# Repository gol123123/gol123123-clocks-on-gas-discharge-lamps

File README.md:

# Clocks-on-gas-discharge-lamps
Мой первый проект с использованием микроконтроллера STM32 и газоразрядных ламп.
# Демонстрация

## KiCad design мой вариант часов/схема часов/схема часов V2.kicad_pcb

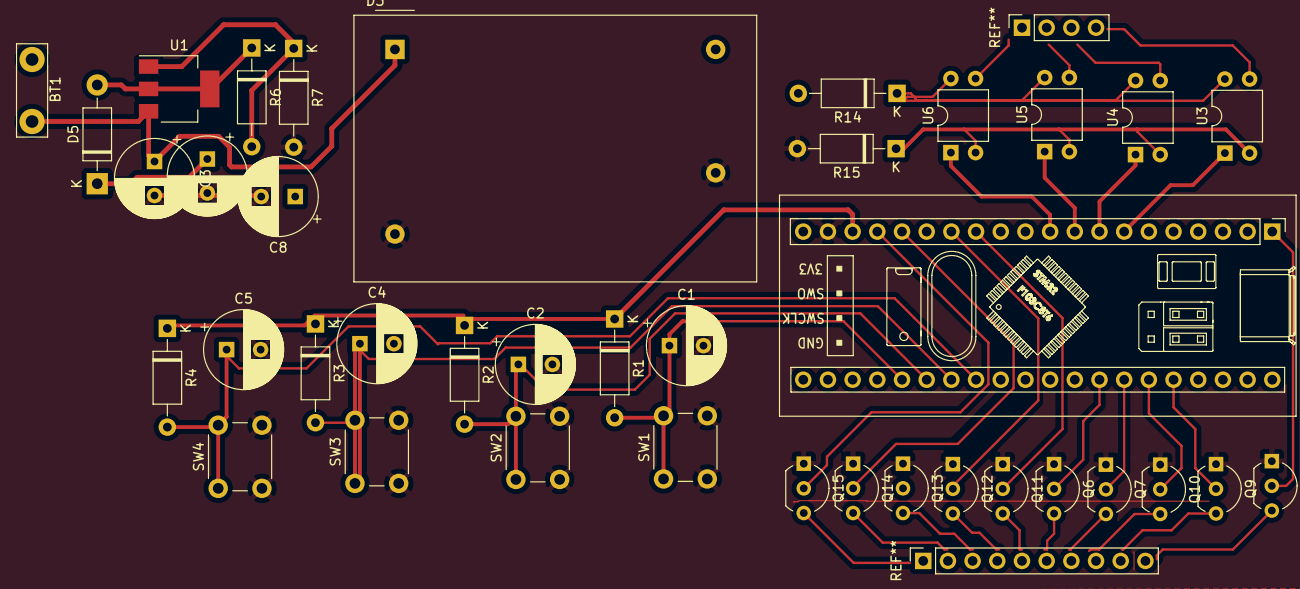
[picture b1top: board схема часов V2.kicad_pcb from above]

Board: 2 copper layers, 38 parts (0 on the bottom side), 26 nets.

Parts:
BT1: Battery_Cell; TestPoint_Bridge_Pitch6.35mm_Drill1.3mm
C1, C2, C4, C5, C8: 1u; CP_Radial_D8.0mm_P3.50mm
C3: 0.1u; CP_Radial_D8.0mm_P3.50mm
C7: 10u; CP_Radial_D8.0mm_P3.50mm
D3: dc-ac_180v; Converter_ACDC_TRACO_TMG-15_THT
D5: 1N4002; D_DO-41_SOD81_P10.16mm_Horizontal
Q6, Q7, Q8, Q9, Q10, Q11, Q12, Q13, Q14, Q15: MPSA42; TO-92_Inline_Wide
R1, R2, R3, R4: 1k; D_A-405_P10.16mm_Horizontal
R6: 4k; D_A-405_P10.16mm_Horizontal
R7: 11k; D_A-405_P10.16mm_Horizontal
R14: 72k; D_A-405_P10.16mm_Horizontal
R15: 470; D_A-405_P10.16mm_Horizontal
SW1, SW2, SW3, SW4: SW_Push; SW_PUSH_6mm
U1: LM317_SOT-223; SOT-223-3_TabPin2
U2: YAAJ_BluePill_Part_Like; YAAJ_BluePill_1
U3, U4, U5, U6: TLP627; DIP-4_W7.62mm

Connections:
/V: C8.1, D5.2, R1.1, R2.1, R3.1, R4.1, R6.1, U1.2, U2.18
/X0: Q15.2, U2.17
/X1: Q6.2, U2.33
/X2: Q7.2, U2.34
/X3: Q8.2, U2.1
/X4: Q9.2, U2.36
/X5: Q10.2, U2.35
/X6: Q11.2, U2.13
/X7: Q12.2, U2.14
/X8: Q13.2, U2.15
/X9: Q14.2, U2.16
/Y1: U2.7, U3.1
/Y2: U2.8, U4.1
/Y3: U2.9, U5.1
/Y4: U2.10, U6.1
/buff_tame_1: C1.1, R1.2, SW1.1, U2.25
/buff_tame_2: C2.1, R2.2, SW2.1, U2.26
/buff_tame_3: C4.1, R3.2, SW3.1, U2.27
/buff_tame_4: C5.1, R4.2, SW4.1, U2.28
GND: C1.2, C2.2, C3.2, C4.2, C5.2, C7.2, C8.2, D3.2, D3.4, Q6.1, Q7.1, Q8.1, Q9.1, Q10.1, Q11.1, Q12.1, Q13.1, Q14.1, Q15.1, R7.2, R15.2, SW1.2, SW2.2, SW3.2, SW4.2, U2.19
unnamed: BT1.1, C3.1, D3.1, U1.3
unnamed: C7.1, D5.1
unnamed: D3.3, R14.2
unnamed: R6.2, R7.1, U1.1
unnamed: R14.1, U3.4, U4.4, U5.4, U6.4
unnamed: R15.1, U3.2, U4.2, U5.2, U6.2

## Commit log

2021-12-29 v1.0
